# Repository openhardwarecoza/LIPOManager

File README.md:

# LIPOManager
18650 Charge Boost based on GreatScott's design

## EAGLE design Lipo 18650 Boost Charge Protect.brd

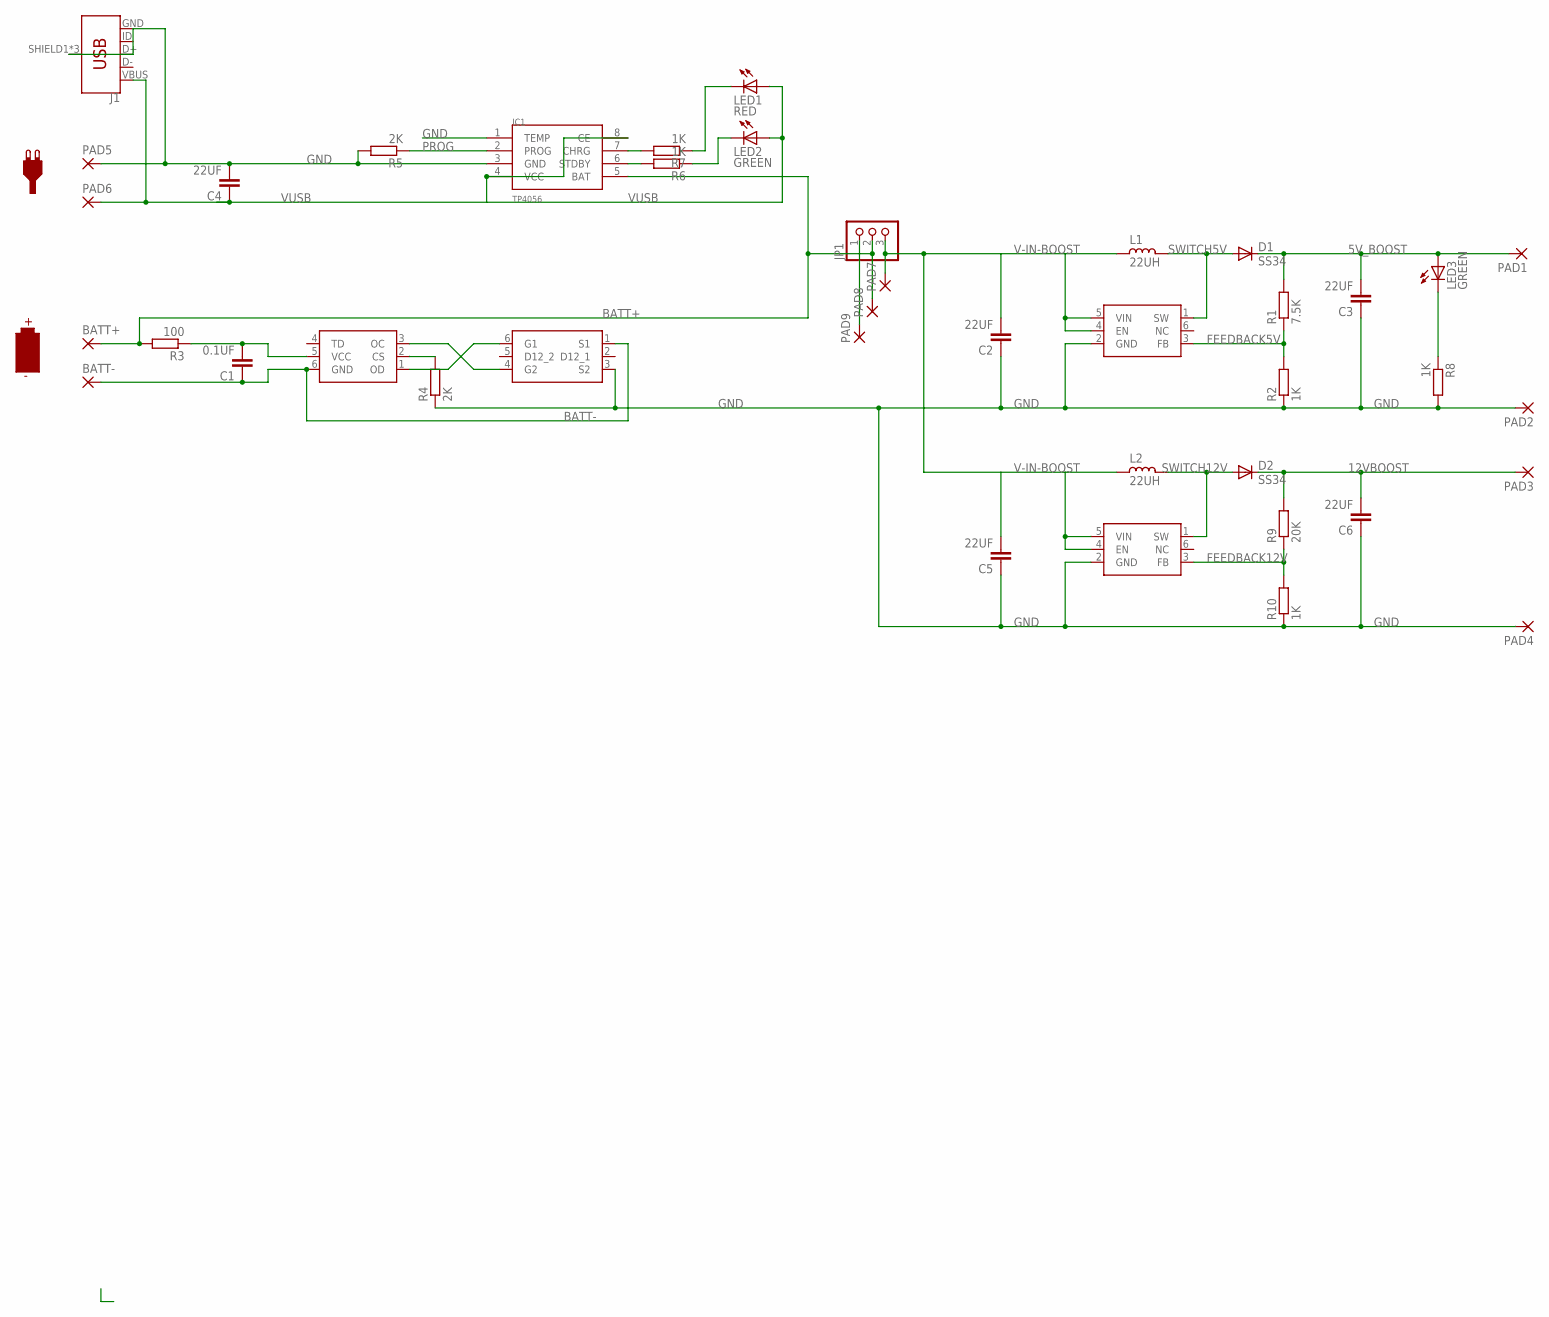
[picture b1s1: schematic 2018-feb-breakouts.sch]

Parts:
BATT+: 3,81/1,4
BATT-: 3,81/1,4
C1: 0.1UF; C1206@1
C2, C3, C4, C5, C6: 22UF; C1812K@1
D1, D2: SS34; DO-214AC
IC1: TP4056; SOP-8
J1: USB_MICRO-B_FEMALE-SMT; USB-B-MICRO-SMD
JP1: PINHD-1X3CB; 1X03-CLEANBIG
L1, L2: 22UH; CD75
LED1: RED; CHIPLED_0805
LED2, LED3: GREEN; CHIPLED_0805
PAD1, PAD2, PAD3, PAD4: SMD5; SMD2,54-5,08
PAD5, PAD6, PAD7, PAD8, PAD9: SMD2; SMD1,27-2,54
R1: 7.5K; R1206
R2, R8, R10: 1K; R1206
R3: 100; R1206
R4, R5: 2K; R1206
R6, R7: 1K; R0603
R9: 20K; R1206
U$1: FS312F-G; SOT23-6
U$2: FS8205; SOT23-6
U$3, U$4: MT3608; SOT23-6

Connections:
5V_BOOST: C3.2, D1.1 (C), LED3.A, PAD1.1, R1.2
12VBOOST: C6.2, D2.1 (C), PAD3.1, R9.2
BATT+: BATT+.1, IC1.5 (BAT), JP1.2, PAD8.1, R3.2
BATT-: BATT-.1, C1.1, U$1.6 (GND), U$2.1 (S1)
CHG: IC1.7 (CHRG), R7.2
FEEDBACK5V: R1.1, R2.2, U$3.3 (FB)
FEEDBACK12V: R9.1, R10.2, U$4.3 (FB)
GND: C2.1, C3.1, C4.2, C5.1, C6.1, IC1.1 (TEMP), IC1.3 (GND), J1.GND, J1.SHIELD1 (SHIELD), J1.SHIELD2 (SHIELD), J1.SHIELD3 (SHIELD), PAD2.1, PAD4.1, PAD5.1, R2.1, R4.1, R5.2, R8.2, R10.1, U$2.3 (S2), U$3.2 (GND), U$4.2 (GND)
LEDCHR: LED1.C, R7.1
LEDSBY: LED2.C, R6.1
unnamed: R4.2, U$1.2 (CS)
unnamed: JP1.1, PAD9.1
unnamed: LED3.C, R8.1
OC: U$1.3 (OC), U$2.4 (G2)
OD: U$1.1 (OD), U$2.6 (G1)
PROG: IC1.2 (PROG), R5.1
STANDBY: IC1.6 (STDBY), R6.2
SWITCH5V: D1.2 (A), L1.1, U$3.1 (SW)
SWITCH12V: D2.2 (A), L2.1, U$4.1 (SW)
V-IN-BOOST: C2.2, C5.2, JP1.3, L1.2, L2.2, PAD7.1, U$3.4 (EN), U$3.5 (VIN), U$4.4 (EN), U$4.5 (VIN)
VCC-PROT: C1.2, R3.1, U$1.5 (VCC)
VUSB: C4.1, IC1.4 (VCC), IC1.8 (CE), J1.VBUS, LED1.A, LED2.A, PAD6.1

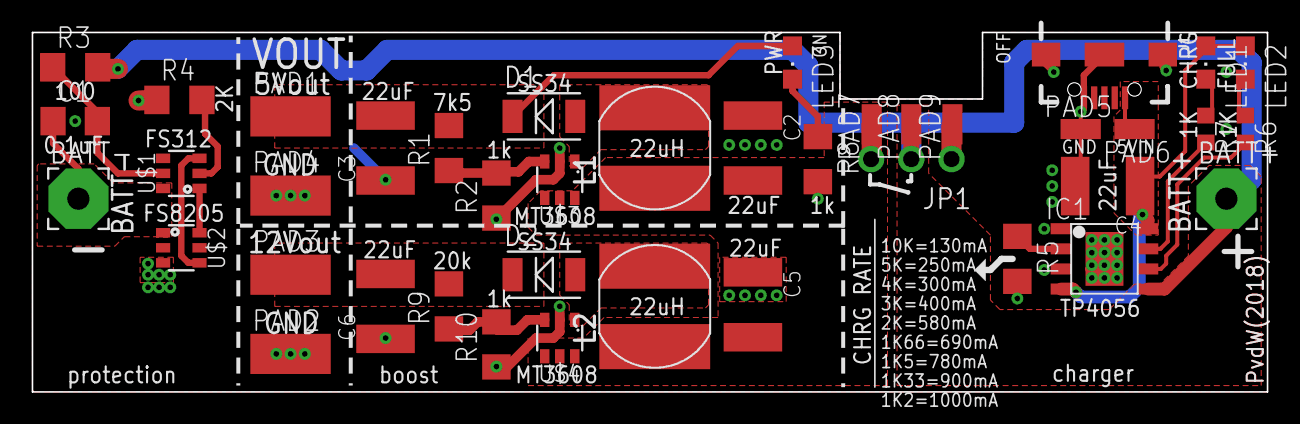
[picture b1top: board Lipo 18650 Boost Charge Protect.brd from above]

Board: 2 copper layers, 78.0 x 22.7 mm, 41 parts (0 on the bottom side), 22 nets.

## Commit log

2018-03-22 first prototype

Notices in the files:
parts and their libraries:
rc-master-smd: Copyright (C) 2007, Bob Starr
SparkFun-Connectors: Licensing: Creative Commons ShareAlike 4.0 International - https://creativecommons.org/licenses/by-sa/4.0
